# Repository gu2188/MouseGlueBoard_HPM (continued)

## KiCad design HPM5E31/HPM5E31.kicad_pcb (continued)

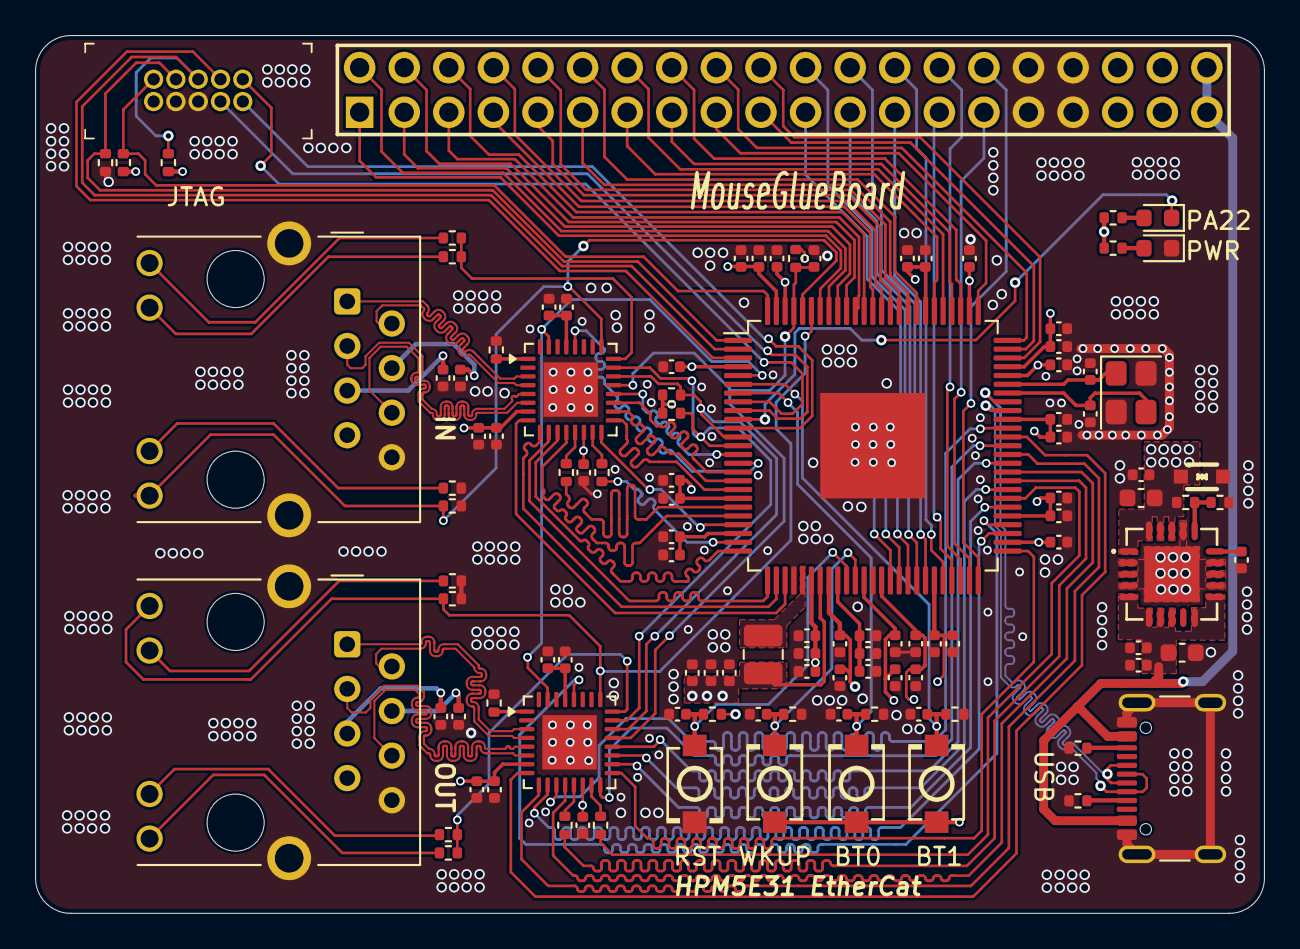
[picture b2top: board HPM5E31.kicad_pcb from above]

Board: 4 copper layers, 70.0 x 50.0 mm, 111 parts (0 on the bottom side), 117 nets.

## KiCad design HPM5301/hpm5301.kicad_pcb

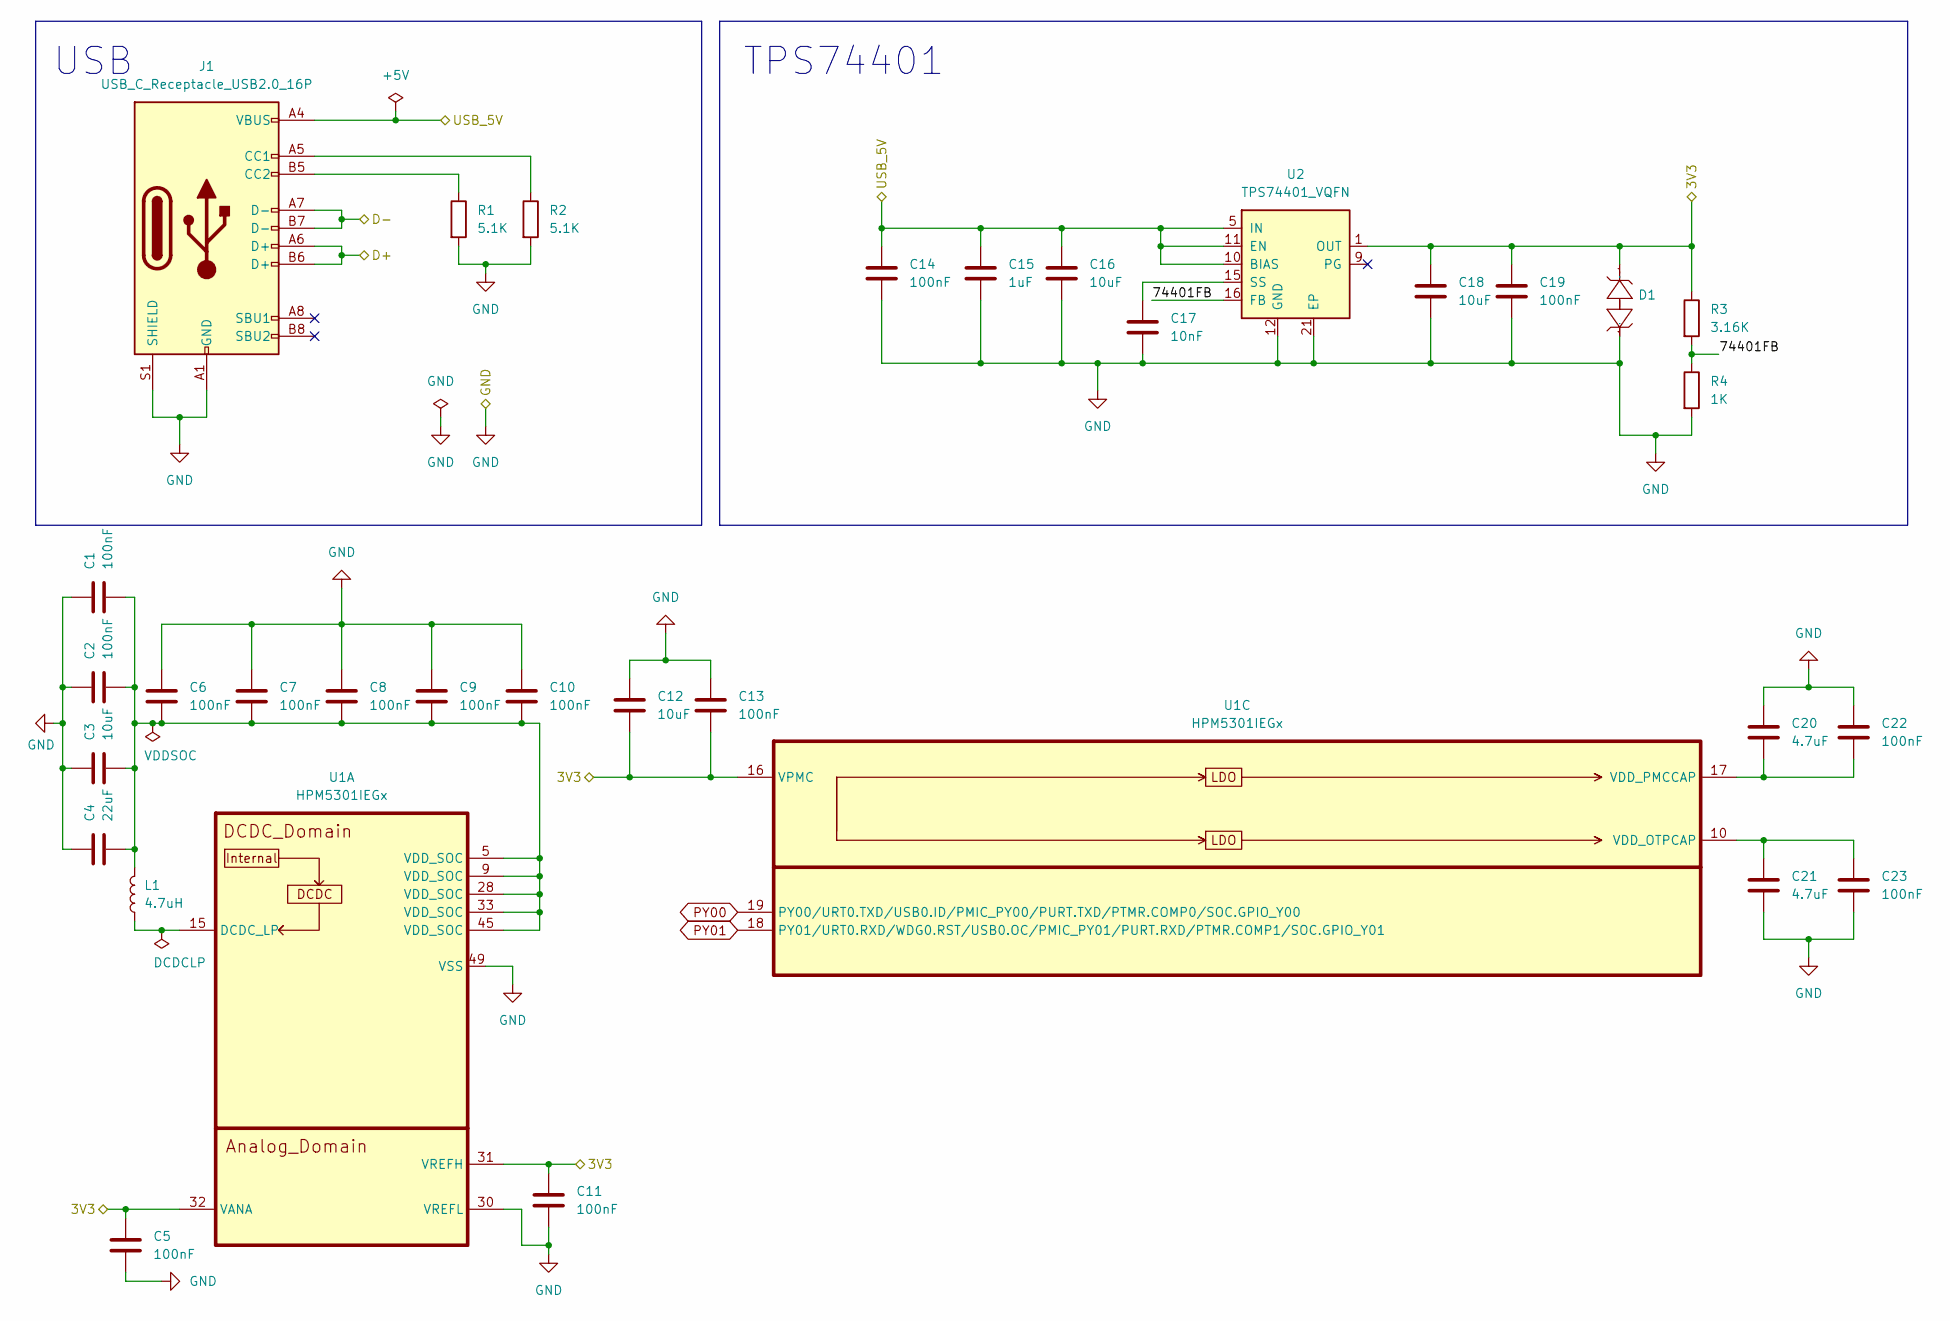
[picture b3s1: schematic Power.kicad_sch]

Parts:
C1, C2, C5, C6, C7, C8, C9, C10, C11, C13, C14, C19, C22, C23: 100nF; C_0402_1005Metric
C3, C12, C16, C18: 10uF; C_0603_1608Metric
C4: 22uF; C_0603_1608Metric
C15: 1uF; C_0402_1005Metric
C17: 10nF; C_0402_1005Metric
C20, C21: 4.7uF; C_0402_1005Metric
D1: SOD-323_L1.7-W1.3-LS2.5-BI; Manufacturer Part PESD3V3L1BA; LCSC Part Name PESD3V3L1BA
J1: USB_C_Receptacle_USB2.0_16P; USB_C_Receptacle_GCT_USB4105-xx-A_16P_TopMnt_Horizontal
L1: 4.7uH; L_1008_2520Metric
R1, R2: 5.1K; R_0402_1005Metric
R3: 3.16K; R_0402_1005Metric
R4: 1K; R_0402_1005Metric
U1: HPM5301IEGx; QFN-48_6x6mm_P0.4mm_EP4.2x4.2mm
U2: TPS74401_VQFN; VQFN-20_L5.0-W5.0-P0.65-TL-EP

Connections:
/IO/3V3: C5.1, C11.1, C12.2, C13.2, C18.1, C19.1, D1.2 (A), R3.1, U1.16 (VPMC), U1.31 (VREFH), U1.32 (VANA), U2.1 (OUT), U2.18 (OUT), U2.19 (OUT), U2.20 (OUT); also elsewhere on the board
/IO/5V: C14.1, C15.1, C16.1, J1.A4 (VBUS), J1.A9 (VBUS), J1.B4 (VBUS), J1.B9 (VBUS), U2.5 (IN), U2.6 (IN), U2.7 (IN), U2.8 (IN), U2.10 (BIAS), U2.11 (EN); also elsewhere on the board
/IO/D+: J1.A6 (D+), J1.B6 (D+); also elsewhere on the board
/IO/D-: J1.A7 (D-), J1.B7 (D-); also elsewhere on the board
/Power/74401FB: R3.2, R4.1, U2.16 (FB)
GND: C1.1, C2.1, C3.1, C4.1, C5.2, C6.1, C7.1, C8.1, C9.1, C10.1, C11.2, C12.1, C13.1, C14.2, C15.2, C16.2, C17.2, C18.2, C19.2, C20.1, C21.2, C22.1, C23.2, D1.1 (K), J1.A1 (GND), J1.A12 (GND), J1.B1 (GND), J1.B12 (GND), J1.S1 (SHIELD), R1.2, R2.2, R4.2, U1.30 (VREFL), U1.49 (VSS), U2.2 (NC), U2.3 (NC), U2.4 (NC), U2.12 (GND), U2.13 (NC), U2.14 (NC), U2.17 (NC), U2.21 (EP); also elsewhere on the board
unnamed: C1.2, C2.2, C3.2, C4.2, C6.2, C7.2, C8.2, C9.2, C10.2, L1.2, U1.5 (VDD_SOC), U1.9 (VDD_SOC), U1.28 (VDD_SOC), U1.33 (VDD_SOC), U1.45 (VDD_SOC)
unnamed: J1.A5 (CC1), R2.1
unnamed: J1.B5 (CC2), R1.1
unnamed: L1.1, U1.15 (DCDC_LP)
unnamed: C21.1, C23.1, U1.10 (VDD_OTPCAP)
unnamed: C20.2, C22.2, U1.17 (VDD_PMCCAP)
unnamed: C17.1, U2.15 (SS)
PY00: U1.19 (PY00/URT0.TXD/USB0.ID/PMIC_PY00/PURT.TX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); also elsewhere on the board
PY01: U1.18 (PY01/URT0.RXD/WDG0.RST/USB0.OC/PMIC_PY0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); also elsewhere on the board

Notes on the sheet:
USB
TPS74401

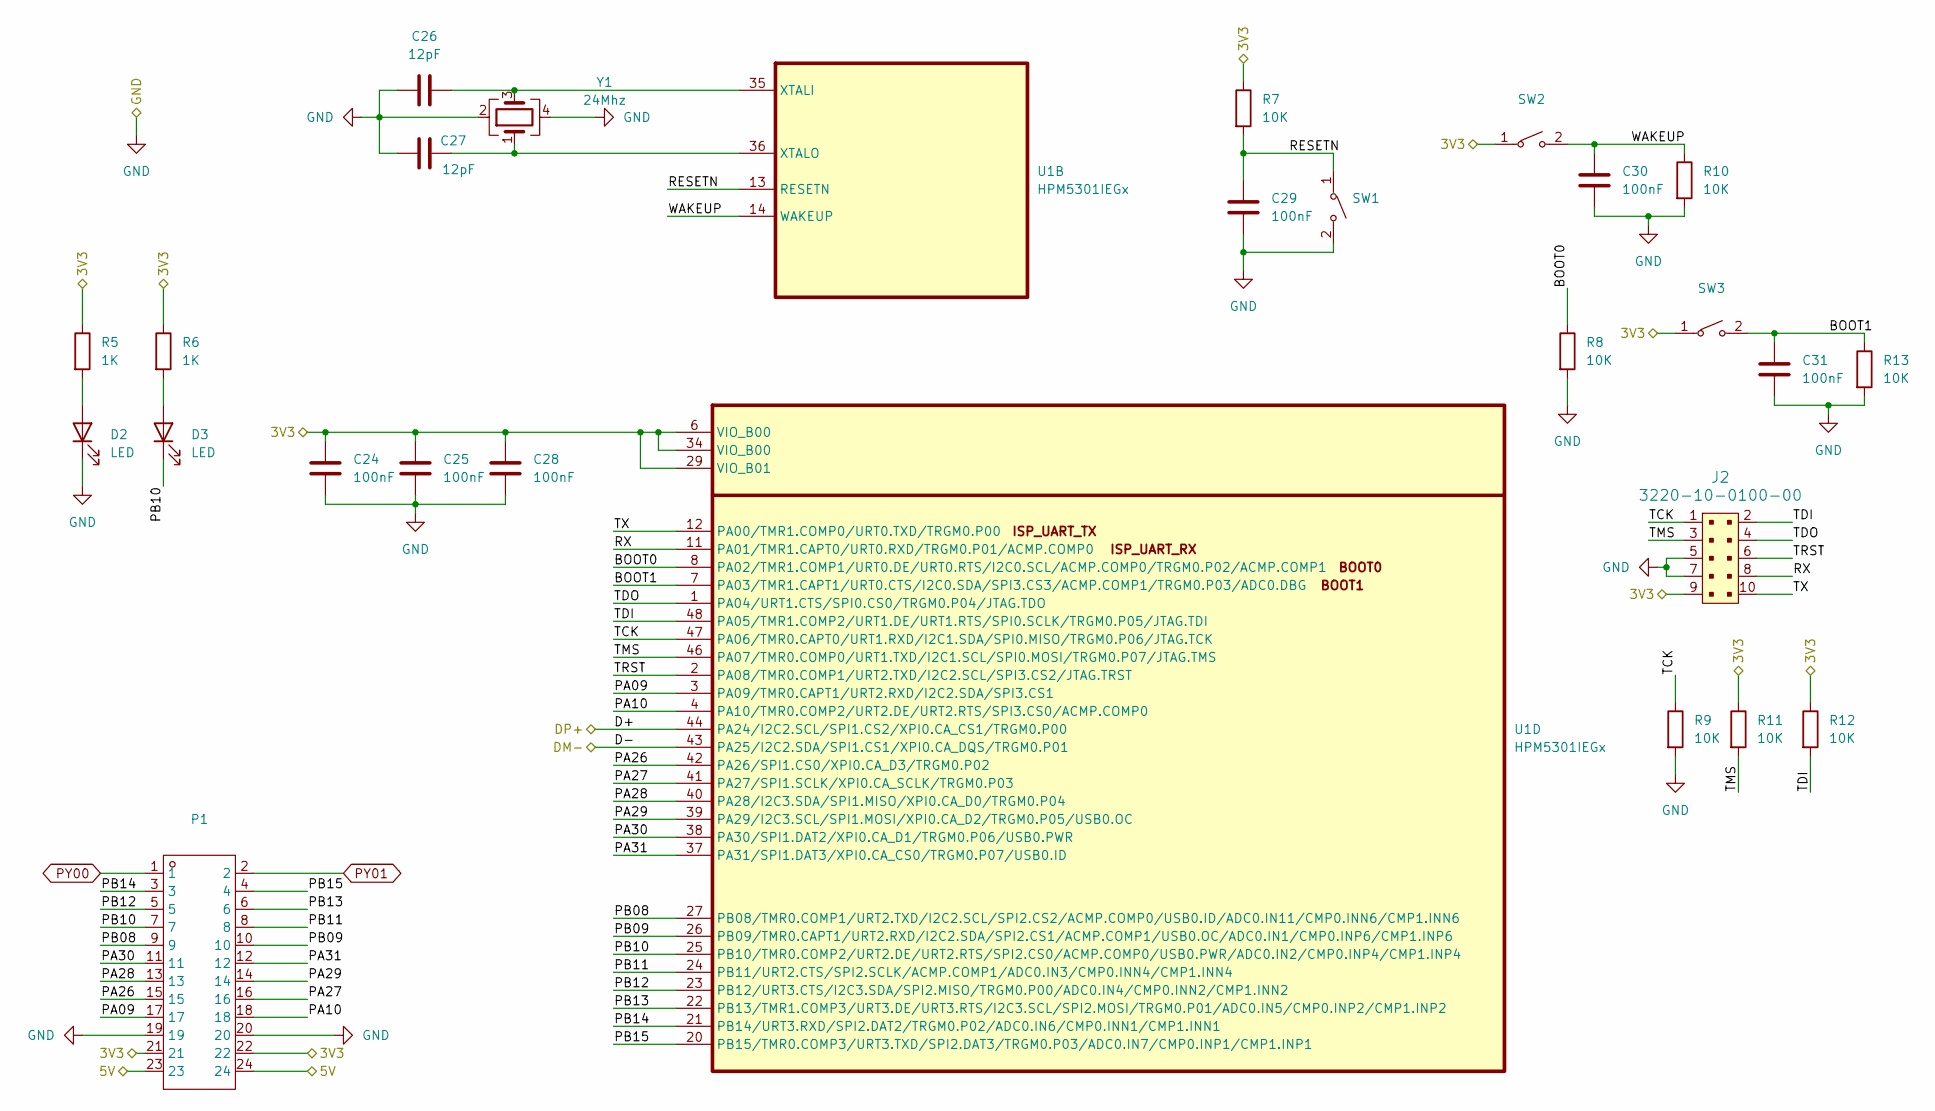
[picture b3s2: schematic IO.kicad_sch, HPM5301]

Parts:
C24, C25, C28, C29, C30, C31: 100nF; C_0402_1005Metric
C26, C27: 12pF; C_0402_1005Metric
D2, D3: LED; LED_0603_1608Metric
J2: 3220-10-0100-00; PinHeader_2x5_P1.27mm_Drill.7mm; MPN 3220-10-0100-00; Digi-Key_PN 1175-1627-ND
P1: HDR-TH_24P-P2.54-V-F-R2-C12-S2.54; Manufacturer Part 2.54-2*12P母; LCSC Part Name 间距:2.54mm 直插
R5, R6: 1K; R_0402_1005Metric
R7, R8, R9, R10, R11, R12, R13: 10K; R_0402_1005Metric
SW1, SW2, SW3: SW-SMD_L3.9-W3.0-P4.45; Manufacturer Part TS-1088R-02026; LCSC Part Name 3.9*2.93*2mm 立贴 轻触开关
U1: HPM5301IEGx; QFN-48_6x6mm_P0.4mm_EP4.2x4.2mm
Y1: 24Mhz; Crystal_SMD_3225-4Pin_3.2x2.5mm

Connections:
/IO/3V3: C24.1, C25.1, C28.1, J2.9, P1.21, P1.22, R5.1, R6.1, R7.1, R11.1, R12.1, SW2.1, SW3.1, U1.6 (VIO_B00), U1.29 (VIO_B01), U1.34 (VIO_B00); also elsewhere on the board
/IO/5V: P1.23, P1.24; also elsewhere on the board
/IO/BOOT0: R8.1, U1.8 (PA02/TMR1.COMP1/URT0.DE/URT0.RTS/I2C0.S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)
/IO/BOOT1: C31.1, R13.1, SW3.2, U1.7 (PA03/TMR1.CAPT1/URT0.CTS/I2C0.SDA/SPI3.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)
/IO/D+: U1.44 (PA24/I2C2.SCL/SPI1.CS2/XPI0.CA_CS1/TRGM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); also elsewhere on the board
/IO/D-: U1.43 (PA25/I2C2.SDA/SPI1.CS1/XPI0.CA_DQS/TRGM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); also elsewhere on the board
/IO/PA09: P1.17, U1.3 (PA09/TMR0.CAPT1/URT2.RXD/I2C2.SDA/SPI3.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)
/IO/PA10: P1.18, U1.4 (PA10/TMR0.COMP2/URT2.DE/URT2.RTS/SPI3.C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)
/IO/PA26: P1.15, U1.42 (PA26/SPI1.CS0/XPI0.CA_D3/TRGM0.P02)
/IO/PA27: P1.16, U1.41 (PA27/SPI1.SCLK/XPI0.CA_SCLK/TRGM0.P03)
/IO/PA28: P1.13, U1.40 (PA28/I2C3.SDA/SPI1.MISO/XPI0.CA_D0/TRGM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)
/IO/PA29: P1.14, U1.39 (PA29/I2C3.SCL/SPI1.MOSI/XPI0.CA_D2/TRGM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)
/IO/PA30: P1.11, U1.38 (PA30/SPI1.DAT2/XPI0.CA_D1/TRGM0.P06/USB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)
/IO/PA31: P1.12, U1.37 (PA31/SPI1.DAT3/XPI0.CA_CS0/TRGM0.P07/US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)
/IO/PB08: P1.9, U1.27 (PB08/TMR0.COMP1/URT2.TXD/I2C2.SCL/SPI2.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)
/IO/PB09: P1.10, U1.26 (PB09/TMR0.CAPT1/URT2.RXD/I2C2.SDA/SPI2.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)
/IO/PB10: D3.1 (K), P1.7, U1.25 (PB10/TMR0.COMP2/URT2.DE/URT2.RTS/SPI2.C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)
/IO/PB11: P1.8, U1.24 (PB11/URT2.CTS/SPI2.SCLK/ACMP.COMP1/ADC0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)
/IO/PB12: P1.5, U1.23 (PB12/URT3.CTS/I2C3.SDA/SPI2.MISO/TRGM0.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)
/IO/PB13: P1.6, U1.22 (PB13/TMR1.COMP3/URT3.DE/URT3.RTS/I2C3.S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)
/IO/PB14: P1.3, U1.21 (PB14/URT3.RXD/SPI2.DAT2/TRGM0.P02/ADC0.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)
/IO/PB15: P1.4, U1.20 (PB15/TMR0.COMP3/URT3.TXD/SPI2.DAT3/TRGM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)
/IO/RESETN: C29.1, R7.2, SW1.1, U1.13 (RESETN)
/IO/RX: J2.8, U1.11 (PA01/TMR1.CAPT0/URT0.RXD/TRGM0.P01/ACMP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)
/IO/TCK: J2.1, R9.1, U1.47 (PA06/TMR0.CAPT0/URT1.RXD/I2C1.SDA/SPI0.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)
/IO/TDI: J2.2, R12.2, U1.48 (PA05/TMR1.COMP2/URT1.DE/URT1.RTS/SPI0.S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)
/IO/TDO: J2.4, U1.1 (PA04/URT1.CTS/SPI0.CS0/TRGM0.P04/JTAG.T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)
/IO/TMS: J2.3, R11.2, U1.46 (PA07/TMR0.COMP0/URT1.TXD/I2C1.SCL/SPI0.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)
/IO/TRST: J2.6, U1.2 (PA08/TMR0.COMP1/URT2.TXD/I2C2.SCL/SPI3.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)
/IO/TX: J2.10, U1.12 (PA00/TMR1.COMP0/URT0.TXD/TRGM0.P00)
/IO/WAKEUP: C30.1, R10.1, SW2.2, U1.14 (WAKEUP)
GND: C24.2, C25.2, C26.1, C27.1, C28.2, C29.2, C30.2, C31.2, D2.1 (K), J2.5, J2.7, P1.19, P1.20, R8.2, R9.2, R10.2, R13.2, SW1.2, Y1.2, Y1.4; also elsewhere on the board
unnamed: D2.2 (A), R5.2
unnamed: D3.2 (A), R6.2
unnamed: C26.2, U1.35 (XTALI), Y1.3
unnamed: C27.2, U1.36 (XTALO), Y1.1
PY00: P1.1; also elsewhere on the board
PY01: P1.2; also elsewhere on the board

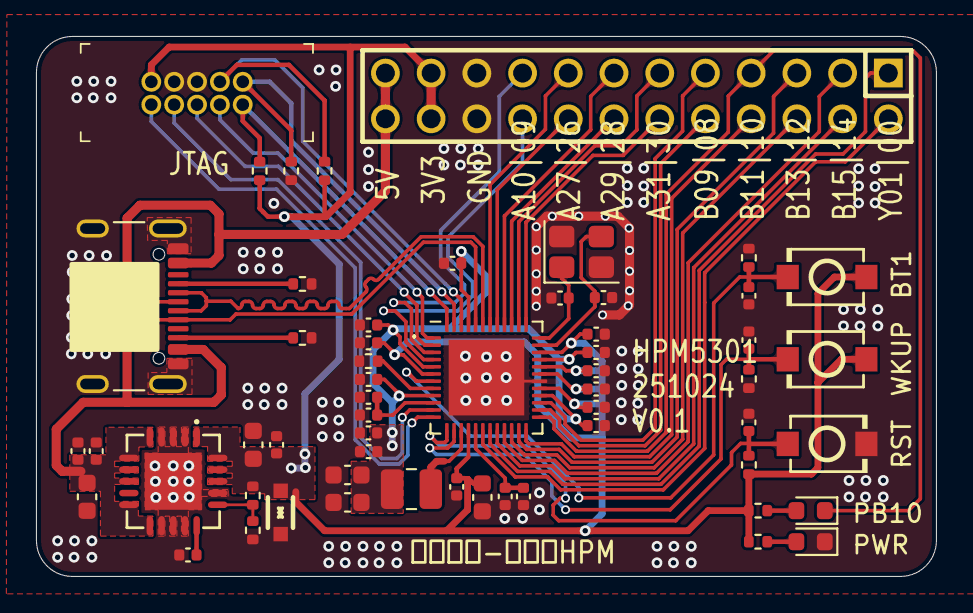
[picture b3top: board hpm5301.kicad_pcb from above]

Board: 2 copper layers, 50.0 x 30.0 mm, 57 parts (0 on the bottom side), 46 nets.

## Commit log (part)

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2025-10-25 更新HPM5301_V0.1版本
2025-11-15 更新HPM5E31_V0.1版本
2025-11-19 更新README.md
2026-01-24 feat:更新HPM5E31_V0.1版本（增加缝合孔）
2026-02-02 feat:修改HPM5E31 SOC电源供电
2026-02-02 feat:增加HPM5E31泪滴
2026-02-02 feat:删除HPM5E31泪滴
2026-05-14 修改gitignore规则，补充部分文件
2026-05-14 feat:更新readme
